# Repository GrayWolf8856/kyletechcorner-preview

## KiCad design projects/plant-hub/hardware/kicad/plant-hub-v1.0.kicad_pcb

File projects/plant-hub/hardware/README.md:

# Plant Hub v1.0 — ESP32-C3 plant watering controller

85 × 60 mm, 2-layer PCB. Drives two 5V LED strip channels (MOSFET low-side),
one pump via a plug-in 5V relay module, and reads an analog soil-moisture
sensor. ESP32-C3 Super Mini is socketed and removable.

## Files

| Path | What |
|---|---|
| `kicad/plant-hub-v1.0.kicad_pro/.kicad_sch/.kicad_pcb` | KiCad 10 project (ERC + DRC clean) |
| `kicad/gen/` | Generators — `netlist.py` is the single source of truth; `gen_libs.py` builds the schematic + libs, `gen/build_pcb.sh` rebuilds the board |
| `manufacturing/plant-hub-v1.0.zip` | **Upload this to JLCPCB** (Gerbers + drill) |
| `manufacturing/plant-hub-v1.0-BOM.csv` | Bill of materials |
| `kicad/plant-hub-v1.0-schematic.pdf` | Printable schematic |
| `kicad/render-top.png`, `render-iso.png` | 3D previews |

## JLCPCB order settings

Defaults are fine. Specifically: 2 layers, 1.6 mm FR-4, 1 oz copper, HASL
(lead-free if offered at no cost), any solder mask color. Min track/space on
this board is 0.25 mm / 0.2 mm — far above their 6 mil (0.152 mm) capability.

## Firmware pin map (ESP32-C3 Super Mini)

| Function | GPIO | Notes |
|---|---|---|
| White LED channel | **6** | HIGH = on |
| Pump | **7** | **HIGH = pump ON** (2N7000 inverts; relay IN is active-low) |
| Grow LED channel | **10** | HIGH = on |
| Soil sensor ADC | **0** | ADC1 — safe to read while WiFi is on |

GPIO2/8/9 are strapping pins and are intentionally unused. Boot-time gate
pulldowns R2/R4 (LEDs) and R7 (pump) keep every output off during reset —
do not omit them.

## Wiring after assembly

- **J1 (5.08 mm)**: 5V PSU in. `+` and `−` marked on silk. The USB-C on the
  ESP32 can stay plugged in at the same time (the module has a protection
  diode), but USB alone cannot power LEDs/pump.
- **J2**: LED strips. `+5` = common +5V to both strips, `W` = white strip
  return (Q1 drain), `G` = grow strip return (Q2 drain).
- **K1 socket**: relay module plugs in here. Order: `V G IN −` (VCC, GND, IN,
  spare). **Verify against your module's silkscreen before plugging in.**
- **J5 → relay contacts**: two short jumper wires: `COM` screw on J5 → COM
  screw terminal on the relay module; `NO` screw on the module → `NO` screw
  on J5. This routes the switched 5V through the board.
- **J3**: pump. `+` = switched 5V (from relay NO via J5), `−` = GND.
- **J4**: soil sensor. `3V3 / GND / SIG` marked. Sensor is 3.3V-only — it is
  wired to the ESP32's 3V3 regulator, never 5V.

## Assembly notes (first-PCB gotchas)

1. **Order of soldering**: SMD resistors/caps first (R1–R6, C2, C3), then
   TO-92/TO-220, then through-hole caps/LED, then sockets and terminal blocks.
2. **C1 polarity**: longer leg = `+`, into the pad nearer the board top edge
   (silk `+`). Stripe on the can = negative side.
3. **D1 polarity**: flat spot / short leg = cathode = toward GND (silk shows outline).
4. **TO-220 (Q1/Q2)**: metal tab faces the top board edge; silk outline makes
   the orientation unambiguous. No heatsink needed at LED-strip currents.
5. **2N7000 (Q3)**: flat face orientation per silk. Pins are S-G-D.
6. **ESP32 socket**: solder the two 1×8 female headers, then plug the module
   in with **USB-C facing the top board edge** (silk says `USB`). With USB up,
   the module's power column (5V/G/3.3 printed on the module) is on the
   RIGHT — the board silk matches this exactly (verified against the standard
   Super Mini pinout). Still eyeball module-silk vs board-silk before first
   power-up; clones occasionally differ.
7. **Smoke test**: before plugging in U1 or the relay module, apply 5V at J1
   and check: D1 lights, 5V on the socket's 5V pin, 3.3V appears only after
   U1 is inserted (the 3V3 rail comes from the module's regulator).

## Design decisions

- Relay is a plug-in module (JQC-3FF-S-Z type) — it already carries the
  transistor, flyback diode and LED, so the board only provides the socket
  and the 2N7000 level/polarity inverter.
- Soil ADC trace runs on the bottom layer, short and straight, with ground
  pour on both layers around it, away from the MOSFET switching area.
- Ground: single GND net, pours on both layers, stitching vias near each
  MOSFET source and around the board.
- Grounded M3 mounting holes (pad+via ring) — metal standoffs tie the frame
  to GND.

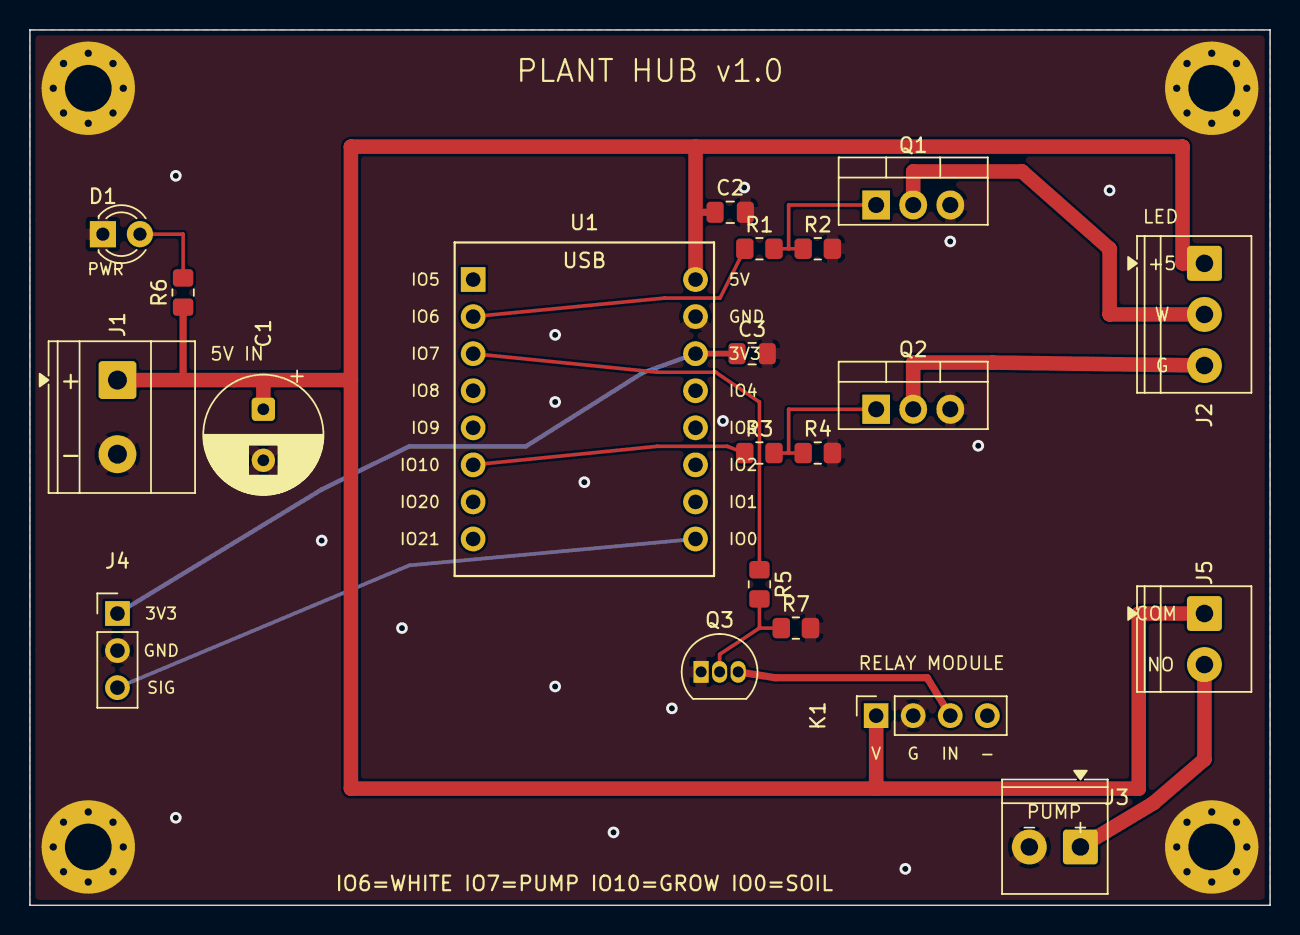
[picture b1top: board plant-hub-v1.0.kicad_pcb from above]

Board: 2 copper layers, 85.0 x 60.0 mm, 25 parts (0 on the bottom side), 15 nets.

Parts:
C1: 470u; CP_Radial_D8.0mm_P3.50mm
C2, C3: 100n; C_0805_2012Metric_Pad1.18x1.45mm_HandSolder
D1: GREEN; LED_D3.0mm
H1, H2, H3, H4: M3; MountingHole_3.2mm_M3_Pad_Via
J1: 5V_IN; TerminalBlock_Phoenix_MKDS-1,5-2-5.08_1x02_P5.08mm_Horizont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
J2: LED_OUT; TerminalBlock_Phoenix_PT-1,5-3-3.5-H_1x03_P3.50mm_Horizontal
J3: PUMP; TerminalBlock_Phoenix_PT-1,5-2-3.5-H_1x02_P3.50mm_Horizontal
J4: SOIL; PinHeader_1x03_P2.54mm_Vertical
J5: RLY_CONTACT; TerminalBlock_Phoenix_PT-1,5-2-3.5-H_1x02_P3.50mm_Horizontal
K1: RELAY_MODULE; PinSocket_1x04_P2.54mm_Vertical
Q1, Q2: RFP30N06LE; TO-220-3_Vertical
Q3: 2N7000; TO-92_Inline
R1, R3: 220; R_0805_2012Metric_Pad1.20x1.40mm_HandSolder
R2, R4, R7: 10k; R_0805_2012Metric_Pad1.20x1.40mm_HandSolder
R5, R6: 1k; R_0805_2012Metric_Pad1.20x1.40mm_HandSolder
U1: ESP32-C3 SuperMini; ESP32-C3-SuperMini-Socket

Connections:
+3V3: C3.1, J4.1, U1.11
+5V: C1.1, C2.1, J1.1, J2.1, J5.1, K1.1, R6.1, U1.9
CTRL_GROW: R3.1, U1.6
CTRL_PUMP: R5.1, U1.3
CTRL_WHITE: R1.1, U1.2
GND: C1.2, C2.2, C3.2, D1.1, H1.1, H2.1, H3.1, H4.1, J1.2, J3.2, J4.2, K1.2, Q1.3, Q2.3, Q3.1, R2.2, R4.2, R7.2, U1.10
G_GROW: Q2.1, R3.2, R4.1
G_PUMP: Q3.2, R5.2, R7.1
G_WHITE: Q1.1, R1.2, R2.1
LED_GROW: J2.3, Q2.2
LED_WHITE: J2.2, Q1.2
PUMP_SW: J3.1, J5.2
PWR_LED: D1.2, R6.2
RELAY_IN: K1.3, Q3.3
SOIL_ADC: J4.3, U1.16

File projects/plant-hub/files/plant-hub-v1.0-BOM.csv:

References,Qty,Value,Part,Description,Footprint
C1,1,470u,470uF 16V radial D8 P3.5,"Bulk input cap (16V preferred, 10V acceptable)",CP_Radial_D8.0mm_P3.50mm
C2 C3,2,100n,0805 100nF X7R,5V decoupling at U1,C_0805_2012Metric_Pad1.18x1.45mm_HandSolder
D1,1,GREEN,LED 3mm green,Power indicator,LED_D3.0mm
J1,1,5V_IN,Screw terminal 2-pos 5.08mm,"5V power input (1=+5V, 2=GND)","TerminalBlock_Phoenix_MKDS-1,5-2-5.08_1x02_P5.08mm_Horizontal"
J2,1,LED_OUT,Screw terminal 3-pos 3.5mm,"LED strips (1=+5V common, 2=WHITE-, 3=GROW-)","TerminalBlock_Phoenix_PT-1,5-3-3.5-H_1x03_P3.50mm_Horizontal"
J3,1,PUMP,Screw terminal 2-pos 3.5mm,"Pump (1=switched +5V from relay NO, 2=GND)","TerminalBlock_Phoenix_PT-1,5-2-3.5-H_1x02_P3.50mm_Horizontal"
J4,1,SOIL,Pin header 1x3 2.54mm,"Soil sensor (1=3V3, 2=GND, 3=AOUT)",PinHeader_1x03_P2.54mm_Vertical
J5,1,RLY_CONTACT,Screw terminal 2-pos 3.5mm,"Jumpers to relay module contacts (1=+5V->COM, 2=NO return)","TerminalBlock_Phoenix_PT-1,5-2-3.5-H_1x02_P3.50mm_Horizontal"
K1,1,RELAY_MODULE,1x4 female header 2.54mm,Socket for 5V relay module JQC-3FF-S-Z (VCC/GND/IN/NC),PinSocket_1x04_P2.54mm_Vertical
Q1 Q2,2,RFP30N06LE,RFP30N06LE,"White LED low-side switch, logic-level NMOS",TO-220-3_Vertical
Q3,1,2N7000,2N7000,Relay-IN inverter (HIGH on GPIO7 = pump ON),TO-92_Inline
R1 R3,2,220,0805 220R 1%,Q1 gate series,R_0805_2012Metric_Pad1.20x1.40mm_HandSolder
R2 R4 R7,3,10k,0805 10k 1%,Q1 gate pulldown - MANDATORY (boot flicker),R_0805_2012Metric_Pad1.20x1.40mm_HandSolder
R5 R6,2,1k,0805 1k 1%,Q3 gate series,R_0805_2012Metric_Pad1.20x1.40mm_HandSolder
U1,1,ESP32-C3 SuperMini,ESP32-C3 Super Mini + 2x female header 1x8 2.54mm,ESP32-C3 Super Mini dev board on 2x 1x8 female headers,ESP32-C3-SuperMini-Socket
H1 H2 H3 H4,4,M3,M3 screw + standoff,Mounting hardware (grounded),MountingHole_3.2mm_M3_Pad_Via

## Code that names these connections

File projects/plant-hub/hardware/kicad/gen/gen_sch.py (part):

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p = pin_pos("U1", "11")  # 3V3
poly([p, (p[0] + 2 * G, p[1]), (p[0] + 2 * G, p[1] + 4 * G)])
power("+3V3", (p[0] + 2 * G, p[1] + 4 * G), "+3V3")
glabel("SOIL_ADC", pin_pos("U1", "16"))
glabel("CTRL_WHITE", pin_pos("U1", "2"), 180)
glabel("CTRL_PUMP", pin_pos("U1", "3"), 180)
glabel("CTRL_GROW", pin_pos("U1", "6"), 180)
for r, n in NL.NO_CONNECTS:
    if r == "U1":
        no_connect(pin_pos("U1", n))
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p = pin_pos("J2", "1")
poly([p, (p[0] - 2 * G, p[1]), (p[0] - 2 * G, p[1] - 2 * G)])
power("+5V", (p[0] - 2 * G, p[1] - 2 * G))
glabel("LED_WHITE", pin_pos("J2", "2"), 180)
glabel("LED_GROW", pin_pos("J2", "3"), 180)

comp("K1", 180, 56)
p = pin_pos("K1", "1")
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p = pin_pos("K1", "2")
poly([p, (p[0] - 4 * G, p[1]), (p[0] - 4 * G, p[1] + 6 * G)])
power("GND", (p[0] - 4 * G, p[1] + 6 * G))
glabel("RELAY_IN", pin_pos("K1", "3"), 180)
no_connect(pin_pos("K1", "4"))

comp("J5", 180, 74)
p = pin_pos("J5", "1")
poly([p, (p[0] - 2 * G, p[1]), (p[0] - 2 * G, p[1] - 2 * G)])
power("+5V", (p[0] - 2 * G, p[1] - 2 * G))
glabel("PUMP_SW", pin_pos("J5", "2"), 180)

comp("J3", 180, 86)
glabel("PUMP_SW", pin_pos("J3", "1"), 180)
p = pin_pos("J3", "2")
poly([p, (p[0] - 2 * G, p[1]), (p[0] - 2 * G, p[1] + 2 * G)])
power("GND", (p[0] - 2 * G, p[1] + 2 * G))
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p = pin_pos("J4", "2")
poly([p, (p[0] - 4 * G, p[1]), (p[0] - 4 * G, p[1] + 4 * G)])
power("GND", (p[0] - 4 * G, p[1] + 4 * G))
glabel("SOIL_ADC", pin_pos("J4", "3"), 180)

# --- notes -------------------------------------------------------------------
text("PUMP LOGIC: Q3 (2N7000) inverts. Relay module IN is active-LOW, so", 118, 96)
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
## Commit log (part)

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2026-06-20 Preview of Kyle Tech Corner public pages
